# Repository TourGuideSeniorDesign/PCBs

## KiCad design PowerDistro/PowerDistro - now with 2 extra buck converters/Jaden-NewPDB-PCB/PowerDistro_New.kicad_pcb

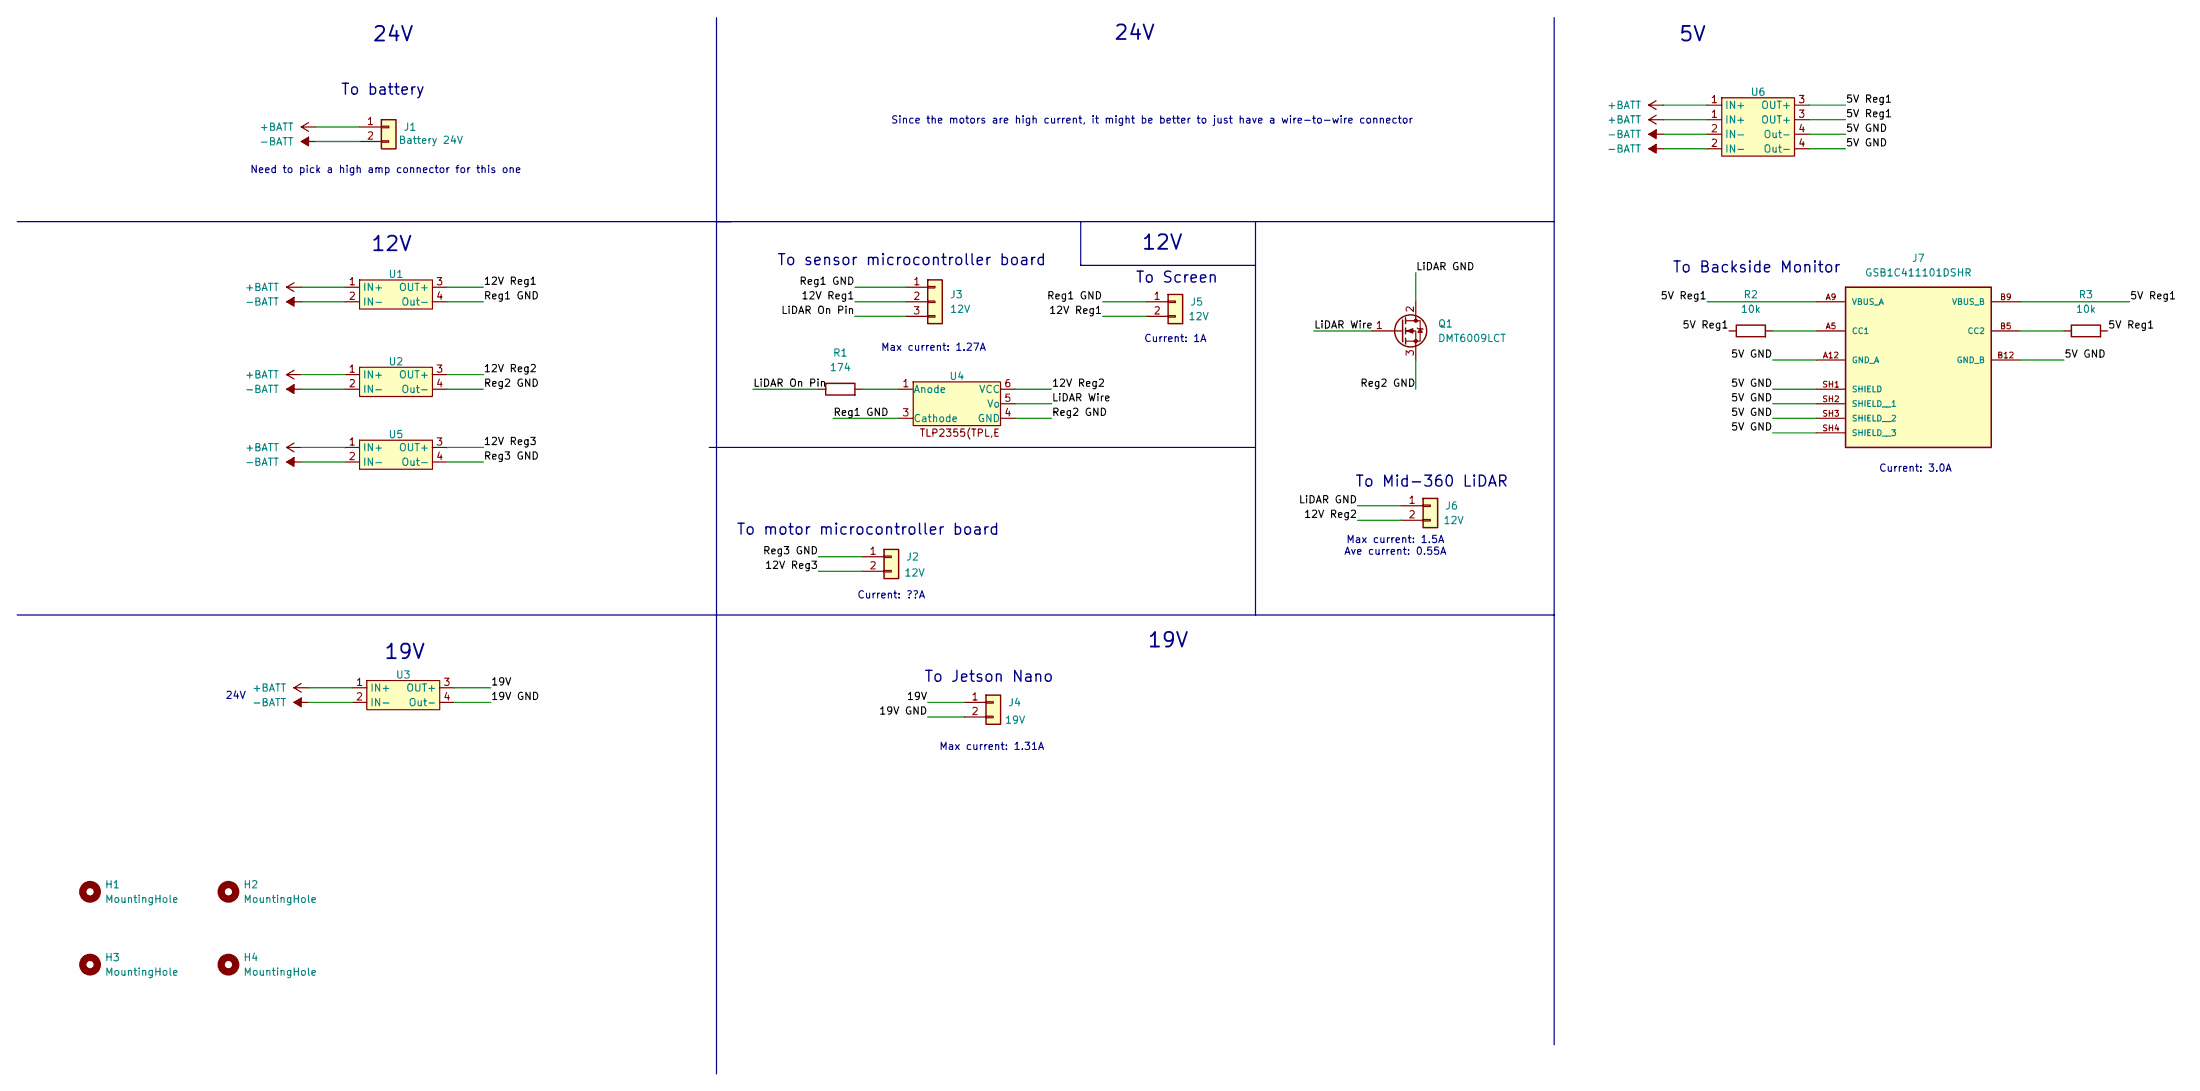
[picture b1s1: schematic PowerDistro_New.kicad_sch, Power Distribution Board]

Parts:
H1, H2, H3, H4: MountingHole; MountingHole_3.2mm_M3_ISO7380_Pad
J1: Molex_Mini-Fit_Jr_5566-02A_2x01_P4.20mm_Vertical; Manufacturer Part Number 0039290023
J2: JST_PH_S2B-PH-SM4-TB_1x02-1MP_P2.00mm_Horizontal; Manufacturer Part Number S2B-PH-SM4-TB
J3: 12V; JST_PH_S3B-PH-SM4-TB_1x03-1MP_P2.00mm_Horizontal; Manufacturer Part Number S3B-PH-SM4-TB
J4, J5, J6: JST_XH_S2B-XH-A-1_1x02_P2.50mm_Horizontal; Manufacturer Part Number S2B-XH-A-1
J7: GSB1C411101DSHR; AMPHENOL_GSB1C411101DSHR; PARTREV AX1
Q1: DMT6009LCT; TO-220-3_Vertical; Manufacturer Part Number DMT6009LCT
R1: 174; R_0805_2012Metric; Manufacturer Part Number RC0805FR-07174RL
R2, R3: 10k; R_0805_2012Metric; Manufacturer Part Number RC0805FR-07174RL
U1, U2, U3, U5: JadenBuck
U4: Optoisolators; SO-5-6_4.55x3.7mm_P1.27mm; Manufacturer Part Number TLP2355(TPL,E
U6: 5V_Buck_Converter_Footprint

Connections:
+BATT: J1.1, U1.1 (IN+), U2.1 (IN+), U3.1 (IN+), U5.1 (IN+), U6.1 (IN+)
-BATT: J1.2, U1.2 (IN-), U2.2 (IN-), U3.2 (IN-), U5.2 (IN-), U6.2 (IN-)
/5V GND: J7.A12 (GND_A), J7.B12 (GND_B), J7.SH1 (SHIELD), J7.SH2 (SHIELD__1), J7.SH3 (SHIELD__2), J7.SH4 (SHIELD__3), U6.4 (Out-)
/5V Reg1: J7.A9 (VBUS_A), J7.B9 (VBUS_B), R2.1, R3.2, U6.3 (OUT+)
/12V Reg1: J3.2, J5.2, U1.3 (OUT+)
/12V Reg2: J6.2, U2.3 (OUT+), U4.6 (VCC)
/12V Reg3: J2.2, U5.3 (OUT+)
/19V: J4.1, U3.3 (OUT+)
/19V GND: J4.2, U3.4 (Out-)
/LiDAR GND: J6.1, Q1.2 (D)
/LiDAR On Pin: J3.3, R1.1
/LiDAR Wire: Q1.1 (G), U4.5 (Vo)
/Reg1 GND: J3.1, J5.1, U1.4 (Out-), U4.3 (Cathode)
/Reg2 GND: Q1.3 (S), U2.4 (Out-), U4.4 (GND)
/Reg3 GND: J2.1, U5.4 (Out-)
unnamed: J7.A5 (CC1), R2.2
unnamed: J7.B5 (CC2), R3.1
unnamed: R1.2, U4.1 (Anode)

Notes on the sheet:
Current: 1A
Current: 3.0A
24V
To Jetson Nano
To battery
19V
12V
Max current: 1.27A
Since the motors are high current, it might be better to just have a wire-to-wire connector
To sensor microcontroller board
To Backside Monitor
To motor microcontroller board
To Mid-360 LiDAR
Need to pick a high amp connector for this one
To Screen
Current: ??A
Max current: 1.5A Ave current: 0.55A
Max current: 1.31A

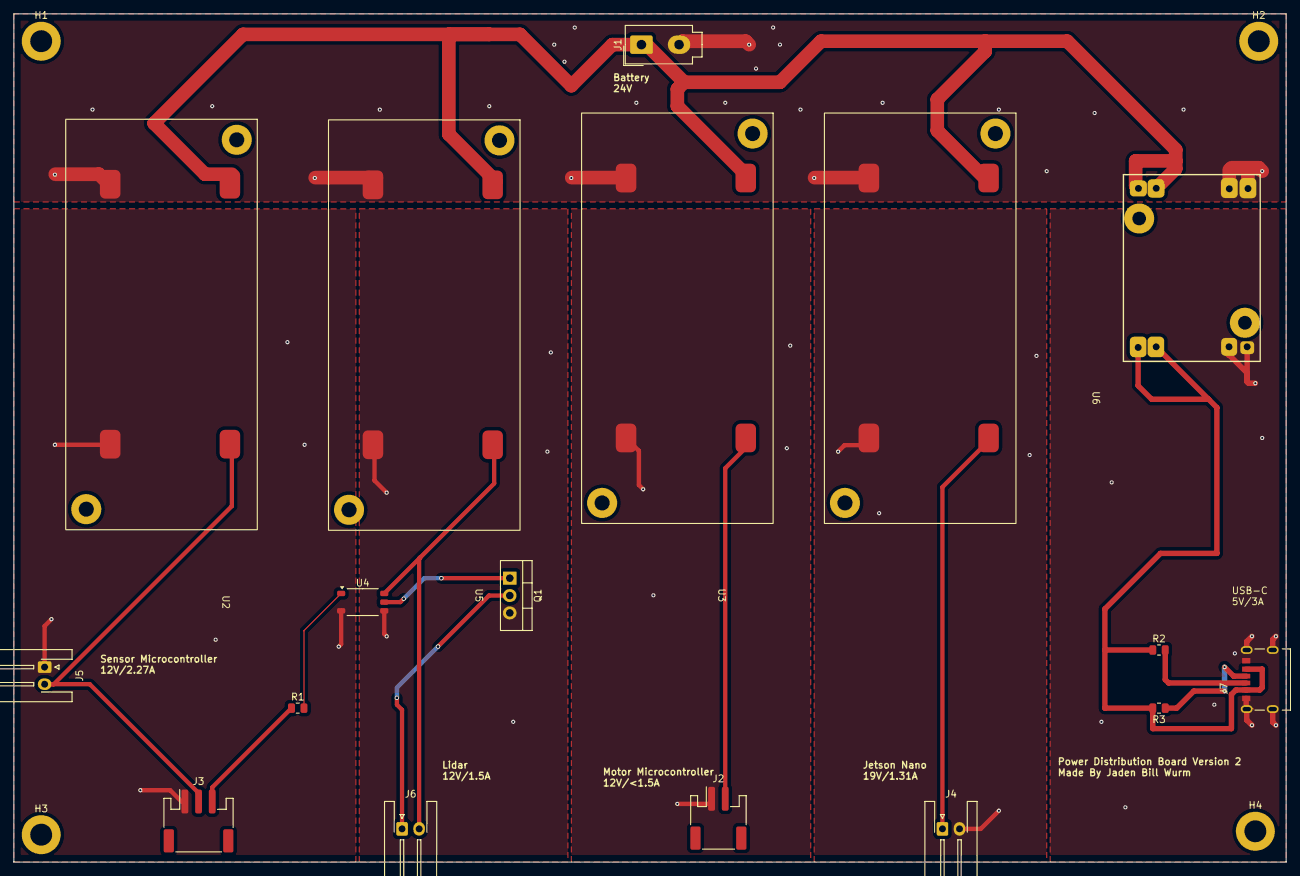
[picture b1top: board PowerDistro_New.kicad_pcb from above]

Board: 2 copper layers, 186.0 x 124.0 mm, 21 parts (0 on the bottom side), 18 nets.
